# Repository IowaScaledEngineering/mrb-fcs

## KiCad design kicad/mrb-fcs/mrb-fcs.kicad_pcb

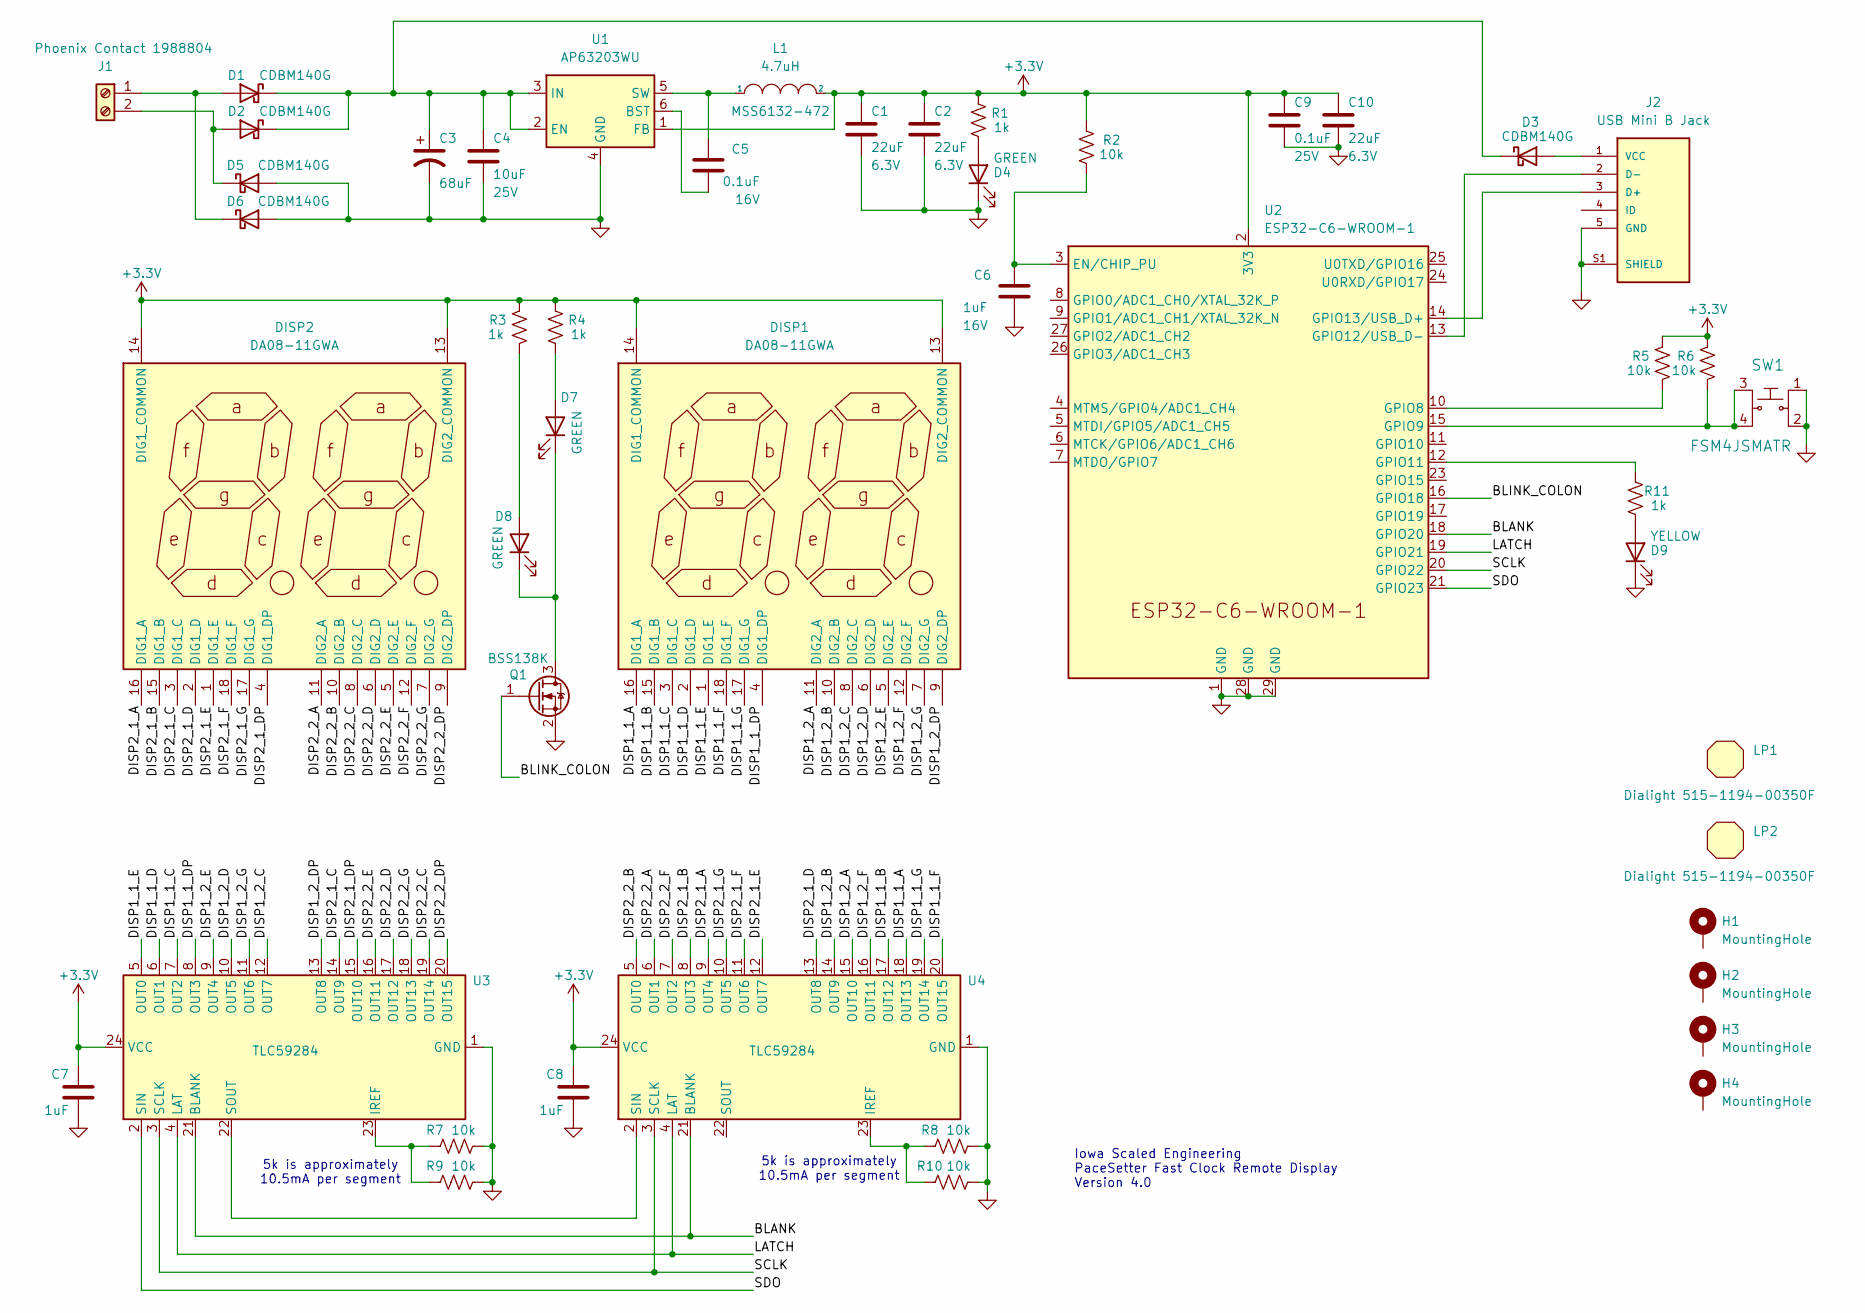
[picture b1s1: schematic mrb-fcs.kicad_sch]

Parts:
C1, C2, C10: 22uF; C_0805_2012Metric; Voltage 6.3V
C3: 68uF; CP_Elec_6.3x5.8
C4: 10uF; C_0805_2012Metric; Voltage 25V
C5: 0.1uF; C_0805_2012Metric; Voltage 16V
C6: 1uF; C_0805_2012Metric; Voltage 16V
C7, C8: 1uF; C_0805_2012Metric; Voltage 6.3V
C9: 0.1uF; C_0805_2012Metric; Voltage 25V
D1, D2, D3, D5, D6: CDBM140G; SOD-123T
D4: GREEN; LED_0805_2012Metric
D7, D8: GREEN; LED_1206_3216Metric_ReverseMount_Hole1.8x2.4mm
D9: YELLOW; LED_0805_2012Metric
DISP1, DISP2: DA08-11GWA; DA08-11; Mouser Part Number 604-DA08-11GWA
H1, H2, H3, H4: MountingHole; MountingHole_3.2mm_M3_Pad
J1: Phoenix Contact 1988804; Phoenix-1988804
J2: USB Mini B Jack; EDAC_690-005-299-043; PARTREV 11
L1: 4.7uH; MSS6132-xxxMLC
LP1, LP2: Dialight 515-1194-00350F; Lightpipe_Dialight_515_1194
Q1: BSS138K; SOT-23
R1, R3, R4, R11: 1k; R_0805_2012Metric
R2, R5, R6, R7, R8, R9, R10: 10k; R_0805_2012Metric
SW1: FSM4JSMATR; TE_FSM4JSMA; MPN FSM4JSMATR; Digi-Key_PN 450-1759-1-ND
U1: AP63203WU; TSOT-23-6
U2: ESP32-C6-WROOM-1
U3, U4: TLC59284; QSOP-24_3.9x8.7mm_P0.635mm

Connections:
+3.3V: C1.1, C2.1, C7.1, C8.1, C9.1, C10.1, DISP1.13 (DIG2_COMMON), DISP1.14 (DIG1_COMMON), DISP2.13 (DIG2_COMMON), DISP2.14 (DIG1_COMMON), L1.2, R1.2, R2.1, R3.2, R4.2, R5.2, R6.2, U1.1 (FB), U2.2 (3V3), U3.24 (VCC), U4.24 (VCC)
/BLANK: U2.18 (GPIO20), U3.21 (BLANK), U4.21 (BLANK)
/BLINK_COLON: Q1.1 (G), U2.16 (GPIO18)
/DISP1_1_A: DISP1.16 (DIG1_A), U4.18 (OUT13)
/DISP1_1_B: DISP1.15 (DIG1_B), U4.17 (OUT12)
/DISP1_1_C: DISP1.3 (DIG1_C), U3.7 (OUT2)
/DISP1_1_D: DISP1.2 (DIG1_D), U3.6 (OUT1)
/DISP1_1_DP: DISP1.4 (DIG1_DP), U3.8 (OUT3)
/DISP1_1_E: DISP1.1 (DIG1_E), U3.5 (OUT0)
/DISP1_1_F: DISP1.18 (DIG1_F), U4.20 (OUT15)
/DISP1_1_G: DISP1.17 (DIG1_G), U4.19 (OUT14)
/DISP1_2_A: DISP1.11 (DIG2_A), U4.15 (OUT10)
/DISP1_2_B: DISP1.10 (DIG2_B), U4.14 (OUT9)
/DISP1_2_C: DISP1.8 (DIG2_C), U3.12 (OUT7)
/DISP1_2_D: DISP1.6 (DIG2_D), U3.10 (OUT5)
/DISP1_2_DP: DISP1.9 (DIG2_DP), U3.13 (OUT8)
/DISP1_2_E: DISP1.5 (DIG2_E), U3.9 (OUT4)
/DISP1_2_F: DISP1.12 (DIG2_F), U4.16 (OUT11)
/DISP1_2_G: DISP1.7 (DIG2_G), U3.11 (OUT6)
/DISP2_1_A: DISP2.16 (DIG1_A), U4.9 (OUT4)
/DISP2_1_B: DISP2.15 (DIG1_B), U4.8 (OUT3)
/DISP2_1_C: DISP2.3 (DIG1_C), U3.14 (OUT9)
/DISP2_1_D: DISP2.2 (DIG1_D), U4.13 (OUT8)
/DISP2_1_DP: DISP2.4 (DIG1_DP), U3.15 (OUT10)
/DISP2_1_E: DISP2.1 (DIG1_E), U4.12 (OUT7)
/DISP2_1_F: DISP2.18 (DIG1_F), U4.11 (OUT6)
/DISP2_1_G: DISP2.17 (DIG1_G), U4.10 (OUT5)
/DISP2_2_A: DISP2.11 (DIG2_A), U4.6 (OUT1)
/DISP2_2_B: DISP2.10 (DIG2_B), U4.5 (OUT0)
/DISP2_2_C: DISP2.8 (DIG2_C), U3.19 (OUT14)
/DISP2_2_D: DISP2.6 (DIG2_D), U3.17 (OUT12)
/DISP2_2_DP: DISP2.9 (DIG2_DP), U3.20 (OUT15)
/DISP2_2_E: DISP2.5 (DIG2_E), U3.16 (OUT11)
/DISP2_2_F: DISP2.12 (DIG2_F), U4.7 (OUT2)
/DISP2_2_G: DISP2.7 (DIG2_G), U3.18 (OUT13)
/LATCH: U2.19 (GPIO21), U3.4 (LAT), U4.4 (LAT)
/SCLK: U2.20 (GPIO22), U3.3 (SCLK), U4.3 (SCLK)
/SDO: U2.21 (GPIO23), U3.2 (SIN)
GND: C1.2, C2.2, C3.2, C4.2, C6.2, C7.2, C8.2, C9.2, C10.2, D4.1 (K), D5.2 (A), D6.2 (A), D9.1 (K), J2.5 (GND), J2.S1 (SHIELD), Q1.2 (S), R7.2, R8.2, R9.2, R10.2, SW1.1, SW1.2, U1.4 (GND), U2.1 (GND), U2.28 (GND), U2.29 (GND), U3.1 (GND), U4.1 (GND)
unnamed: D1.2 (A), D6.1 (K), J1.1
unnamed: C3.1, C4.1, D1.1 (K), D2.1 (K), D3.1 (K), U1.2 (EN), U1.3 (IN)
unnamed: D2.2 (A), D5.1 (K), J1.2
unnamed: D3.2 (A), J2.1 (VCC)
unnamed: D4.2 (A), R1.1
unnamed: D7.2 (A), R4.1
unnamed: D7.1 (K), D8.1 (K), Q1.3 (D)
unnamed: D8.2 (A), R3.1
unnamed: D9.2 (A), R11.1
unnamed: J2.3 (D+), U2.14 (GPIO13/USB_D+)
unnamed: J2.2 (D-), U2.13 (GPIO12/USB_D-)
unnamed: C5.2, U1.6 (BST)
unnamed: C5.1, L1.1, U1.5 (SW)
unnamed: C6.1, R2.2, U2.3 (EN/CHIP_PU)
unnamed: R5.1, U2.10 (GPIO8)
unnamed: R6.1, SW1.3, SW1.4, U2.15 (GPIO9)
unnamed: R11.2, U2.12 (GPIO11)
unnamed: R7.1, R9.1, U3.23 (IREF)
unnamed: U3.22 (SOUT), U4.2 (SIN)
unnamed: R8.1, R10.1, U4.23 (IREF)

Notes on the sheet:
5k is approximately 10.5mA per segment
Iowa Scaled Engineering PaceSetter Fast Clock Remote Display Version 4.0

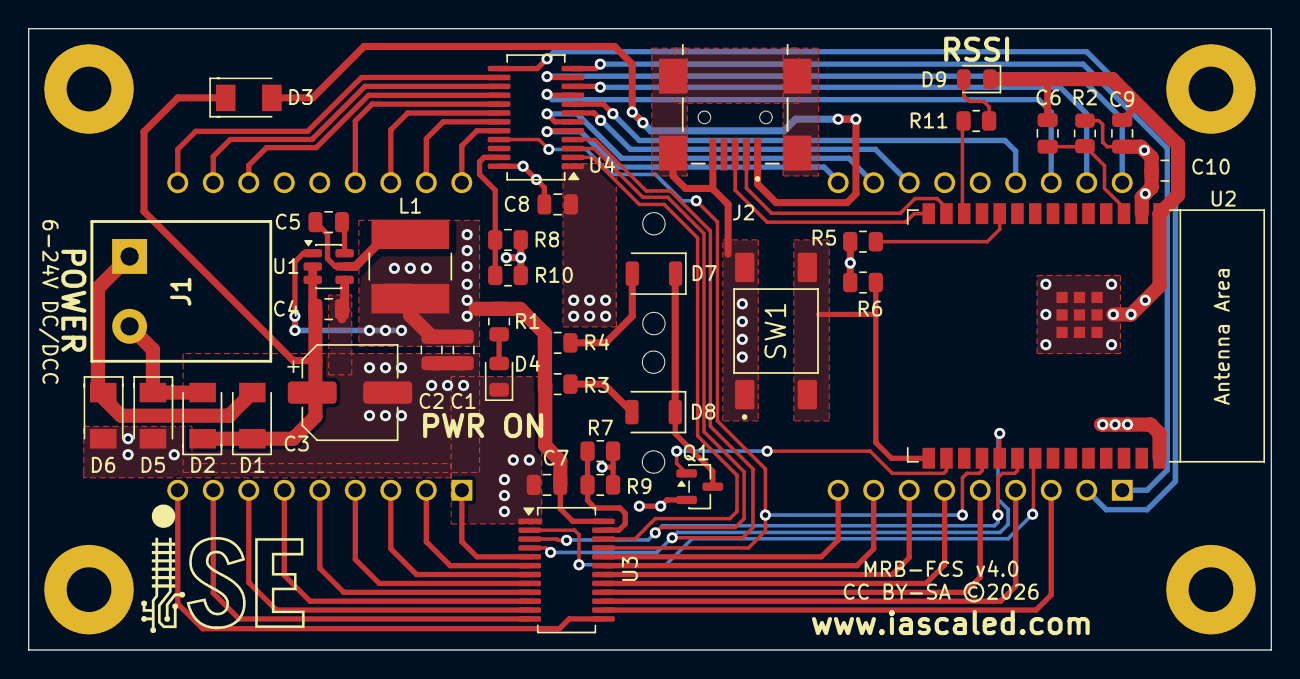
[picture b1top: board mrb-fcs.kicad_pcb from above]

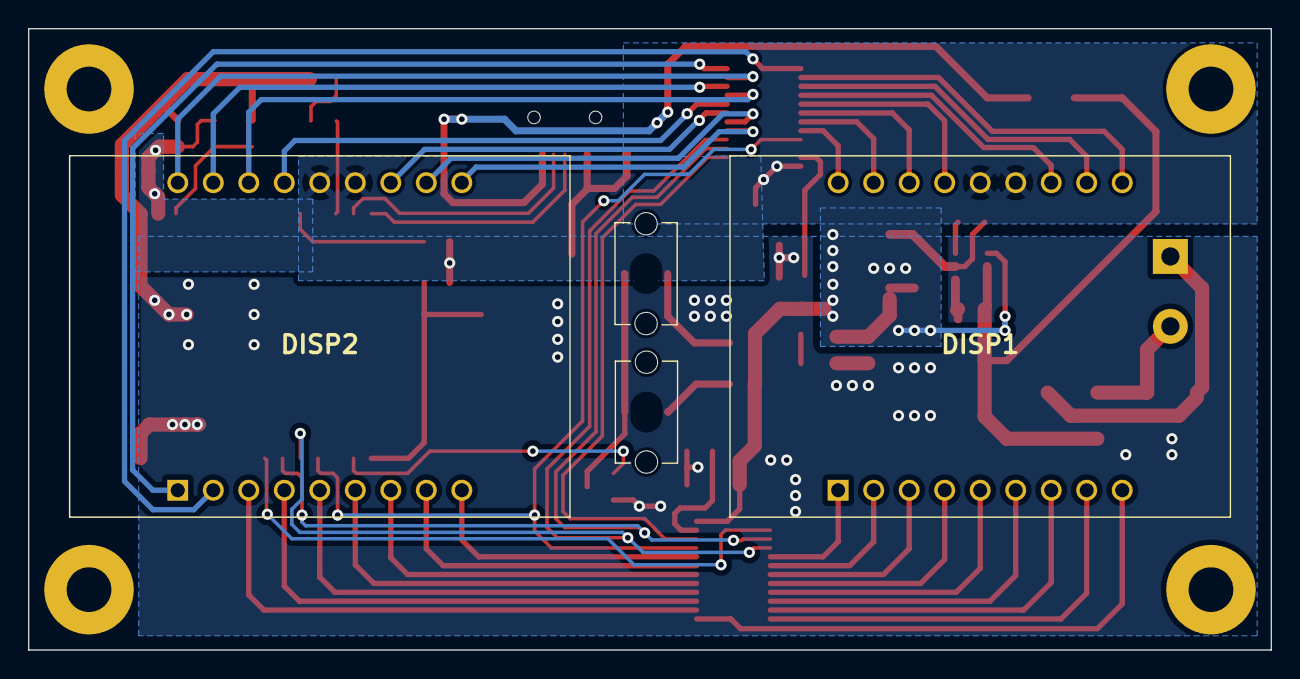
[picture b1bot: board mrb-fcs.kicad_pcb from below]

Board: 2 copper layers, 88.9 x 44.4 mm, 47 parts (4 on the bottom side), 59 nets.

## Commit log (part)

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2012-06-01 Added new project - fast clock slave
2012-06-01 Removed thermals on regulator to get more metal.
2012-07-08 Initial cut of the firmware, aligning pins to the final production units
2012-07-31 Respond to time packets
2012-07-31 Added initial dead reckoning code to deal with missing time packets
2012-11-04 Change to allow for nodes without flow control lines
2012-11-05 Add ADC stuff - don't promise this actually works yet
2012-11-07 Sync with work changes and make it compile
2012-11-07 Made it initialize to --:-- correctly
2012-11-08 Modified to take a 2 byte ratio, in x:10 form
2012-11-08 Created the fcs pg stuff - shouldn't have changed since I created the v1.0 board
2012-11-13 Cleanup wired vs wireless
2012-12-16 Fixed version packet info.
2013-01-03 Fixed silkscreen on holes and TQFP32. Schematic now references TQFP32 footprint (not _7)
2013-01-03 Changed rev to 1.1 due to previous soldermask edits
2013-02-03 LVS/DRC Clean.
2013-02-03 Added copyright. LVS/DRC Clean.
2013-02-03 Added PG files.
2013-02-05 Changed large (60/35) vias to standard (40/20) vias to make freedfm happy. LVS/DRC Clean.
2013-02-05 New PG.
2013-03-03 Fixed colon fade. DDRD should have bit 3 (PD3) set as output.
2014-03-25 Various fixes to make it compile now
2014-08-01 Update screw hole sizes to 0.148" to clear #6 screw
2014-09-11 Added atomic block around fast time increment routine
2015-07-26 Added include
2015-11-11 Add mrbus submodule
2015-11-11 Conversion to mrbus2 (mrbus from git) libraries
2016-03-27 Installation example
2016-11-05 New version of the FCS - wired and wireless - using LED drivers rather than indivudual discretes
2016-11-05 Fix refdeses and schottky
2016-11-06 Finished PCB and schematic
2016-11-06 Add + signs to LEDs
2016-11-07 Various fixes
2016-11-07 Move holes to 170mil from edge Add outline layer
2016-11-18 Add v2 pg
2016-11-20 Add I2C lib
2016-11-21 Fix lack of pullups on the I2C lines and make first version of working code
2016-11-21 Fix makefile, update avr-i2c library
2016-11-21 Update version number Add thermal vias in the TLC59116 pads - not sure this will manufacture yet, but want to create pg to try it out
2016-11-21 Make a few ISR variables static rather than global volatile
2016-11-21 Fix for moving of global ISR variables - forgot to remove initializers later in the code
2017-02-15 Add pg 2.1
2017-06-02 Decreased solder paste aperature on the QFN32 footprint. Bumped rev to 2.2 Changed (C) to 2017
2017-06-02 Smaller QFN stencil aperture
2017-06-18 Fixed power-up delays causing XBee to go into command mode
2020-02-25 v3 rework in progress
2020-02-25 Removed extra shapes
2020-02-25 Fixed erratic colon (separated time flags from status flags)
2020-02-25 Fixed some volatiles
2020-03-08 Partial route
2020-03-08 Done routing, needs optimization
2020-03-09 Removed C3. Cleanup
2020-03-09 Moved C4 to other side of AVR. More cleanup
2020-03-10 Cleanup
2020-03-10 Added RJ11
2020-03-10 Moved J3 text. Remove thin GND plane sections near A/B terminals.
2020-03-10 Removed square pads on J1/J2
2020-03-10 Widened 3.3V plane near R8
2020-04-17 Cleaned up some metal and text
2020-04-17 Added U6 and fixed R2 connections
2020-04-17 Moved C9 away from C10
2020-04-17 Moved AVR right 40mil
2020-04-17 Reduced via sizes in a few places and improved GND plane metal
2020-04-17 Minor tweaks
2020-04-23 Edits from Nathan's review
2020-04-29 Fixed title block. DRC/LVS clean.
2020-06-11 Add initial cut of I2C-FCS python control code
2020-06-13 Files sent to fab
2020-06-13 Moved J5/C7 text to better attach C7 to its footprint
2020-06-13 Added /RST pullup (R3)
2020-06-14 Replaced RECOM with AP63205
2020-06-14 Added C2A
2020-06-21 Lowered brown-out level
2020-07-04 Sent to fab 7/2
2021-02-17 Add segment check and version number to startup of FCS
2021-02-17 Modify startup digit test sequence
2021-07-27 Box label
2021-07-27 Box for sitting on table
2021-11-19 Updated label

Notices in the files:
kicad/mrb-fcs/mrb-fcs.kicad_pcb:
CC BY-SA ©2026
